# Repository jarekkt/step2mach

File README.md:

# step2cnc
Plugin for Mach3 and Nucleo-F429ZI  board

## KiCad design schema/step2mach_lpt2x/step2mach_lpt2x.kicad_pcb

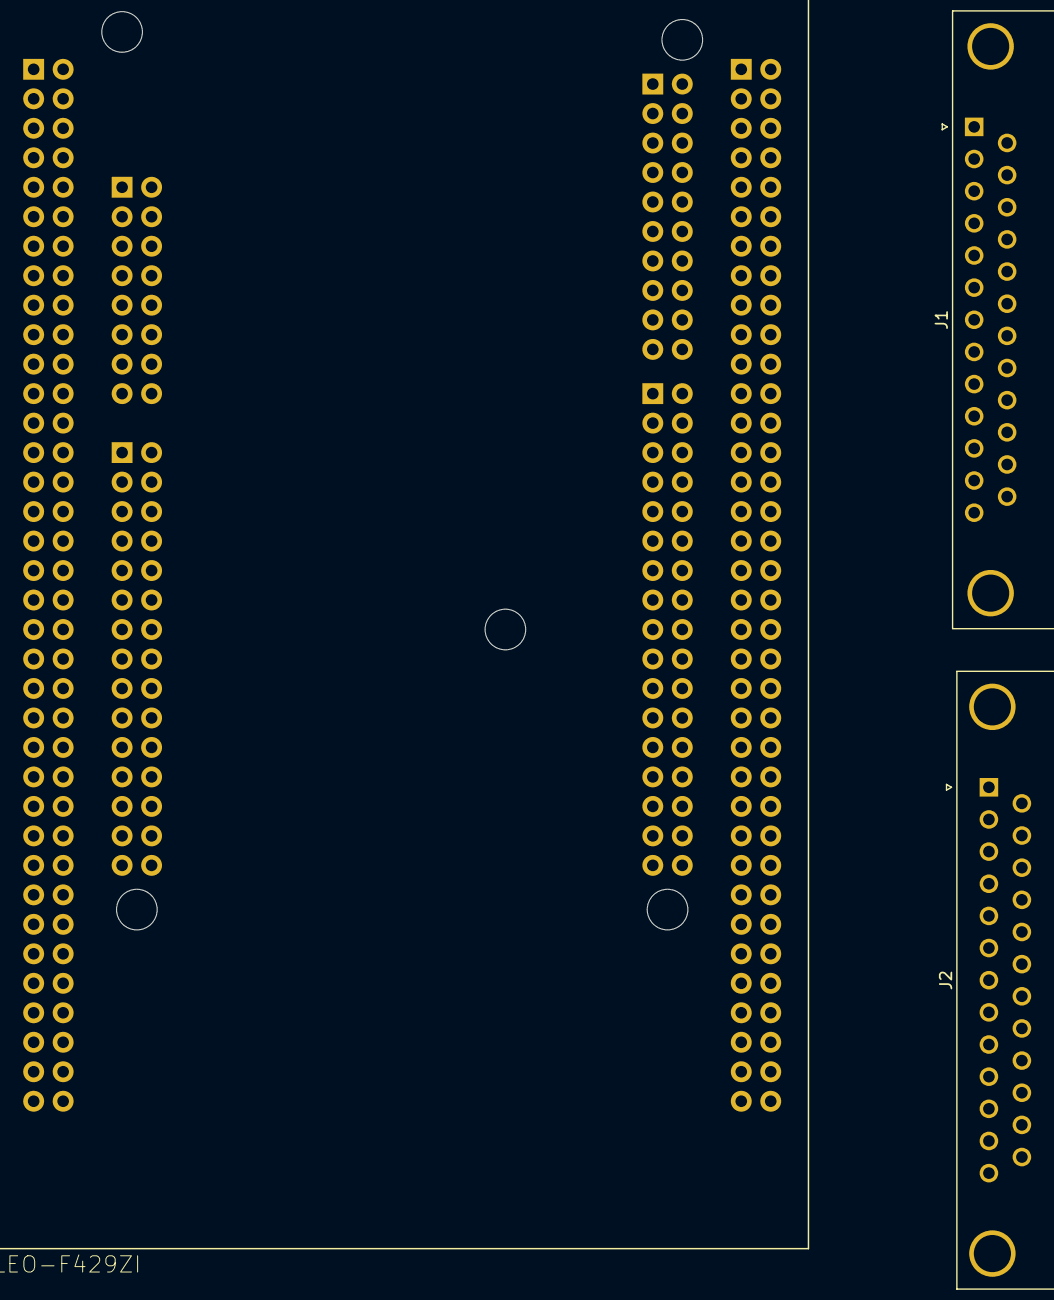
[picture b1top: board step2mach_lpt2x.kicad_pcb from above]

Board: 2 copper layers, 3 parts (0 on the bottom side), 5 nets, no tracks yet.

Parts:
J1: DB25_Male_MountingHoles; DSUB-25_Female_Horizontal_P2.77x2.84mm_EdgePinOffset7.70mm_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
J2: DB25_Male_MountingHoles; DSUB-25_Female_Horizontal_P2.77x2.84mm_EdgePinOffset4.94mm_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
U1: NUCLEO-F429ZI; MODULE_NUCLEO-F429ZI

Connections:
unnamed: U1.CN8_11, U1.CN8_13
unnamed: U1.CN9_12, U1.CN9_23
unnamed: U1.CN10_5, U1.CN10_17, U1.CN10_22, U1.CN10_27
unnamed: U1.CN11_8, U1.CN11_19, U1.CN11_20, U1.CN11_22, U1.CN11_49, U1.CN11_60, U1.CN11_71, U1.CN11_72
unnamed: U1.CN12_9, U1.CN12_20, U1.CN12_39, U1.CN12_54, U1.CN12_63, U1.CN12_71, U1.CN12_72

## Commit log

2019-04-07 Cleanup - also final Crossworks files added
2019-04-09 Net is working.
2019-04-10 First port ready ( however no testing yet)
2019-04-10 First communication with Mach3
2019-04-11 Second LPT port added. Cleaned variable types.
2019-04-11 First running version. Connects to Mach3
2019-04-12 TrueStudio project file added
2019-04-12 Clean compile for TrueStudio
2019-04-13 Checked for compilation under Windows
2019-04-15 License added
2019-05-19 GCode movement fix.
    There were problems with UDP frame MTU size after changing data types for some variables - now dynamic calculation.
    Also fixed free slot calculation ( also after cleaning old code)
2019-05-19 New definitions generated from MX ( to fit the real hardware)
2019-06-04 Changed default IP and changed pinouts
2019-06-19 GCODE runner fix. Full Mach3 SDK added
2019-06-21 Fixes in timing and pin control (missing mapping)
2020-03-07 `vallen` is verified to be less than `len`, therefore, it can never be the case that `vallen >= len + sizeof(rhostname)`.
    This PR fixes the check so the `rhostname` array does not overflow.
    Reported-by: Github Security Lab <securitylab@github.com>
